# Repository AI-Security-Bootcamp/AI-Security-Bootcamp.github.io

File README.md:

# AI Security Bootcamp

Website for the AI Security Bootcamp, built with [Next.js](https://nextjs.org).

**Live site:** https://ai-security-bootcamp.github.io/

## Development

Use Node.js 24 (also used in CI) and npm. `package-lock.json` is the sole lockfile;
the obsolete pnpm lockfile has been removed.

```bash
npm ci
npm run dev
```

Open [http://localhost:3333](http://localhost:3333) to view the site.

Check dependency advisories with `npm audit`, including development tools. After
updates, run typechecking, lint, unit tests, and the production browser suite.
Next.js route parameters are asynchronous, and Tailwind 4's theme configuration
lives in `src/app/globals.css`.

The `serve` dependency currently pins `compression` to vulnerable version 1.8.1.
The scoped npm override selects patched 1.8.2 or later; remove it once `serve`
updates its dependency. See the [compression advisory](https://github.com/advisories/GHSA-vc2v-76pw-4v95).

Next's ESLint plugin uses `fast-glob` only for `globSync` root-directory discovery.
Its scoped override uses a small adapter in `tools/next-eslint-glob` backed by
Node's built-in `fs.globSync` (stable in Node 22.17+) to remove the unpatched
[`braces` vulnerability](https://github.com/advisories/GHSA-vfj7-8cjw-p6xm).
A unit test exercises that plugin integration; review the override when upgrading
`eslint-config-next` and remove it once upstream replaces the vulnerable chain.
ESLint stays on 9.39.5 because the React, import, and accessibility plugins still
declare ESLint 9 as their highest compatible major version.

## Deployment

The site automatically deploys to GitHub Pages when changes are pushed to the `main` branch via GitHub Actions.

To build locally:

```bash
npm run build
```

Static files are output to the `out/` directory.

## City program shortcuts

`/london`, `/sf` (or `/san-francisco`), `/vegas`, and
`/singapore` show that city's latest program and update the URL to its dated
program page, preserving query parameters and anchors. The latest program is
the one with the greatest start date across all years, including past, current,
and upcoming cohorts, regardless of whether applications are open.

City routes are generated from `src/lib/cohorts.ts` during each build. Register
each program component in `src/app/_program-pages.ts`; new location slugs get
their own city shortcut automatically. Alternate city names are defined in
`src/lib/city-programs.ts`. Year-specific aliases such as `/london26` and `/sf26`
continue to point to their original cohorts.

## Homepage film

The homepage uses `src/components/HeroFilm.tsx` and the versioned, static media
package in `public/video/aisb-hero-v5/`. No streaming service or server runtime is
needed: these files are included in the normal GitHub Pages export.

- The workshop thumbnail stays still and is clickable. The opening preloads
  through the bounded adaptive buffer, but playback requires a click or Enter.
- Playback starts with sound and the browser's standard controls; no duplicate
  toolbar, silent looping preview or automatic restart on scroll/tab return.
- The film pauses when offscreen or in a hidden tab. Resume is always explicit.
- Native HLS where supported; otherwise dynamically loaded `hls.js`, with
  automatic 360p/540p/720p/1080p quality switching and aligned two-second segments.
- The JavaScript player starts at 360p and caps quality to the displayed size;
  Safari's native player manages its own quality selection. A 540p
  fast-start MP4 is the fallback for unsupported HLS or fatal streaming errors.
- The same opt-in behavior applies to reduced motion, Save-Data and 2G users.
- The thumbnail is keyboard accessible and transfers focus to the native player.
  Burned-in captions and the music attribution in the media package remain.
  No separate transcript/credits row is displayed beneath the hero.

The thumbnail uses the original workshop photograph: instructor, raised hand and
attendees, with “A week at AISB” and a centered red, square play overlay rendered as HTML/CSS.
There is no location label or duration badge. The photograph and encoded film are unchanged.
On phones, the original larger typography is restored, with side-by-side buttons
and reduced top padding. Text, video and carousel follow their natural content
height with 24 px around the video, without stretching to fill tall screens.
The theme toggle floats independently with a 44 px touch target; desktop keeps the
spacious two-column hero.
The player preserves the full 16:9 picture rather than cropping the speakers or
captions. All 29 caption boxes have equal 16 px vertical padding in the master.

To encode a replacement from a corrected master and its lossless audio mix:

```bash
python3 videos/encode_web.py path/to/master.mp4 \
  --audio-master path/to/delivery-master.wav \
  --timeline path/to/timeline.json \
  --output public/video/aisb-hero-v6
```

Requires FFmpeg/ffprobe and Python 3.11+. The encoder refuses to overwrite an
existing package and verifies full decoding, aligned keyframes, source hashes,
and the MP4 fast-start header. Update `mediaRoot` in `HeroFilm.tsx` to the new
version after encoding. The current package's `encoding.json` records sizes and
checks. Retain the transcript and music credit when moving the files; an external
media host would also need appropriate CORS and HLS/MP4 content types.

The TypeScript browser suite covers preloading, responsive/dark-mode thumbnails,
keyboard activation, sound-on playback, seeking, no looping, explicit resume,
reduced motion/data saving, declined playback, HLS failure fallback, and a real
throttled bandwidth downshift. Native Safari playback still needs a real-device
check. Local tests and builds do not publish the site.

## Testing

Use Node.js 20.19+ (or 22.12+ / 24+) and npm. Install the test browser once:

```bash
npm ci
npx playwright install --with-deps --only-shell chromium
```

```bash
npm test                 # Vitest unit and server-rendered component tests
npm run test:watch       # Watch unit tests while editing
npm run typecheck        # Check application code, tests, and test configs
npm run test:e2e         # Build, start a static preview, run Chromium, then stop it
npm run test:e2e:ui      # Playwright's interactive test runner
npm run test:hero        # Only the homepage layout and video browser tests
npm run test:all         # Typecheck, unit tests, and all browser tests
```

Tests live in `tests/unit/*.test.ts` and `tests/e2e/*.spec.ts`. Vitest handles
TypeScript and JSX directly. Playwright provides isolated browser contexts,
shared fixtures, named tests, failure screenshots/traces, and an HTML report.
Browser tests serve the production export to exercise the same directory routes
as GitHub Pages. They block external requests, including analytics and live forms.
The slower bandwidth-adaptation check is included in the normal browser suite.

To target specific tests or use an existing server:

```bash
npm test -- city-programs
npm run test:e2e -- city-aliases
PLAYWRIGHT_BASE_URL=http://127.0.0.1:3333 npm run test:e2e
npx playwright show-report
```

Set `PLAYWRIGHT_CHROMIUM_EXECUTABLE` only if using an existing Chromium binary.
Artifacts go to ignored `test-results/` and `playwright-report/` directories.
Pull requests run typechecking, lint, unit tests, and browser tests. Main-branch
builds pass the same checks before deployment.

## Signup experiments (October 2026)

The homepage always lists cohorts accepting applications first and marks each
cohort's application status. The programme menu is labelled “View programmes”.

The **SF mobile Apply** experiment is running in PostHog project 324798:

| Experiment | Feature flag | Primary conversion |
| --- | --- | --- |
| [SF mobile Apply](https://us.posthog.com/project/324798/experiments/501073) | `signup-sf-mobile-apply-v1` | Click any Airtable application link; individual new CTA usage is secondary |

The flag uses equal `control` / `test` variants. The treatment adds a fixed bottom
Apply button and another after Cost & Selection. Mobile eligibility is determined
at page load with a viewport below 768 CSS pixels. The buttons hide on wider
screens after resizing.

The [homepage essentials](https://us.posthog.com/project/324798/experiments/501071)
and [SF essentials](https://us.posthog.com/project/324798/experiments/501072) tests
were stopped on 21 October 2026, and their flags were disabled. The summary blocks
and their assignment code have been removed. Their historical results remain in
PostHog; the early samples were insufficient for a reliable conversion conclusion.

`src/lib/mobile-apply-experiment.ts` reads the mobile flag without the SDK's
automatic exposure event. It emits `signup_experiment_exposed` after the assigned
UI is committed, with `experiment`, `variant`, `page`, `mobile_apply_variant`, and
`$feature/<flag-key>` properties. Missing, disabled or blocked flags retain the
normal page and emit no exposure. The
PostHog experiment uses that custom exposure, production host filters, exclusion
of test accounts and a 30-minute conversion window. The application CTAs also emit
`application_form_clicked` for actual form destinations, while keeping existing
click events and adding `cohort_id`, `destination` and `href` to them.

Analytics keeps `persistence: 'memory'`. Assignment stays fixed for the current
page load; a reload or document navigation can produce a new identity/variant.
These are **page-load comparisons, not unique-person or completed-application
conversion rates**. Do not join homepage and SF loads as a cross-page funnel.
Before 21 October at 22:44 UTC, the mobile test could overlap with the SF essentials
test. Keep that change in context when comparing results before and after removal.
The small mobile audience may not yield a conclusive result before applications
close. Secondary CTA usage alone is not evidence of overall improvement.

Check exposure balance and production application-link events before interpreting
results. End the mobile test by **8 November 2026 at 11:59:59 UTC** (the 7 November AoE
deadline). The client also stops enrolling new page loads after that deadline or
when the SF cohort's application mode is closed. Disable the corresponding flag
to return new loads to the original layout. Do not persist analytics IDs to make
assignments sticky without a separate privacy decision.

`tests/e2e/signup-experiments.spec.ts` mocks PostHog and intercepts all analytics
traffic. It checks control/treatment exposures, delayed and disabled flags,
mobile and desktop eligibility, the deadline, CTA destinations, footer clearance
and the existing cookie/localStorage behaviour.

## Video-generation source

The reusable renderers, edit plans, selections and review templates are in
[videos/](videos/README.md), with one flat folder per edit and shared helpers.
Run `python3 videos/run.py list` to see the available commands. Raw/private inputs
and generated assets stay in the ignored media workspace; they are not needed in
Git. The previous `scripts/encode-hero.py` command remains a compatibility wrapper.

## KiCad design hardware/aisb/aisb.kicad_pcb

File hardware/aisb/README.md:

# AISB e-paper badge

The current saved design is `aisb.kicad_pcb`, with project settings in
`aisb.kicad_pro`. Earlier Vegas/London copies are preserved in Git; see
[hardware history and layout](../README.md). Commit revisions to these stable
filenames. The design notes below describe the original prototype architecture;
the saved PCB includes subsequent manual KiCad edits.

## Render badge images

With Python 3 and Pillow installed, run from the repository root:

```bash
python3 hardware/aisb/scripts/render-web-badge.py \
  --first-name Pranav --last-name Gade --role speaker
```

The bundled font and website logo are selected automatically. Black/red flashing
planes and a matching preview go to the ignored `out/flash/` directory. Use
`--output-dir` to choose another location. Monochrome nametags use
`scripts/render-nametag.py`; arbitrary artwork uses `scripts/render-three-color-art.py`.
The source for the balloon artwork is `assets/artwork/girl-with-balloon.jpg`.

The three-color panel writer is `scripts/write_image_b.py`; it expects the
Waveshare driver checkout under `scripts/driver/` on the programming machine.
The monochrome programmer and its setup instructions are in `firmware/`.

### Small 250 × 122 name-only badge

```bash
python3 hardware/aisb/scripts/render-small-badge.py --name "Byron Alvarez"
```

This separate layout uses IBM Plex Mono Bold, all caps, black text on white,
and nothing else. It fits one or two lines using actual ink bounds, centers
them with 10px minimum margins, and saves a true 1-bit PNG to `out/small/`.
It never accesses the Pi or a display. The existing 360 × 240 flash helper
is **not compatible**. A separate `write_image_2in13_v4.py` and the recovery
kit's `flash-small-badge.sh` support the confirmed Waveshare 2.13-inch V4
monochrome panel; see [setup and switch settings](../epaper/README.md).
Tests: `python3 hardware/aisb/scripts/test-small-badge.py`.

## Hardware overview

This revision is a 100 x 145 mm conference badge built around the
[Waveshare 3.52-inch raw black/white e-paper panel](https://www.waveshare.com/3.52inch-e-paper.htm).
The screen is large enough for a readable name and role, while the upper PCB
remains visible for the AISB logo and copper artwork.

The badge has no microcontroller, USB connector, battery, MIDI keys, or touch
controls fitted by default. Instead:

- the 360 x 240 e-paper glass is centred on the front of the badge;
- its actual 3.65 +/- 0.30 mm electrical FPC, as dimensioned in the
  [Waveshare V1.1 panel drawing](https://files.waveshare.com/wiki/3.52inch%20e-Paper%20HAT/3.52inch%20e-Paper%20V1.1.pdf), stays straight into a low-profile
  front-side ZIF immediately left of the glass; the drawing's 10 mm feature is
  only a removable adhesive-tape pull-tab, and there is no internal flex
  cutout;
- the badge carries the small passive high-voltage support circuit required by
  the raw panel;
- a reusable external programmer supplies 3.3 V, ground, and SPI/control through
  the zero-height Tag-Connect `J3` target;
- optional `J4` is a passive 1 x 8, 2.54 mm through-hole interface for a short
  ribbon harness to a removable Waveshare ESP32 Driver Board V3; the module is
  powered only through its own USB-C connector, its onboard FPC stays empty,
  and the carrier provides only passive slots and a nonconductive spacer/retainer;
- a standard-polarity rear-silkscreen QR links to `https://aisb.dev/badge0`; and
- a two-layer PCB pickup coil remains available as a passive electromagnetic
  audio sensor.

After an external programmer refreshes the screen and is removed, the image
remains visible without power. Each badge therefore needs the comparatively
expensive controller only while its name is being written.

## Important status

This is a prototype design, not a production release. The current 24-pin panel
table and an older application-circuit drawing in Waveshare's documentation
are not completely consistent. Before ordering production quantity:

1. Buy one exact panel SKU/revision and the proposed 24-position ZIF.
2. Verify the flex contact side, pin 1, insertion direction, glass dimensions,
   and complete straight-tail/connector fit against the physical parts.
3. Assemble 3-5 badges and validate every generated e-paper rail during a
   refresh with a current-limited bench supply.
4. Confirm that the display survives repeated mounting and programming cycles.
5. Run KiCad DRC and have an experienced PCB designer review the high-voltage
   support circuit, footprint geometry, and assembly files.
6. If the optional ESP32 path is considered, measure at least three exact Rev 3
   modules, continuity-test the passive harness, and validate the mounting
   slots/spacer, USB clearance, retention/drop loads, and worn-badge RF range.
   There is no onboard power isolation: never attach or power two controllers.

Do not send the generated board straight to a production run.

For the current two-week deadline, follow
[`docs/two-week-release-plan.md`](docs/two-week-release-plan.md). The custom
on-board circuit remains the primary path, with five engineering units tested
first. Every raw panel is also pre-written off-board before mounting. Two
official Waveshare Driver HAT stations provide an independent fallback by
writing the raw panel flex directly; they do not bypass the badge through
`J3`. See [`docs/hat-fallback.md`](docs/hat-fallback.md).

For the two-week schedule, buy **both types of universal driver**: two
[Universal Driver HATs](https://www.waveshare.com/e-paper-driver-hat.htm) as the
Raspberry-Pi-friendly production fallback, and at least three exact
[ESP32 Driver Board V3](https://www.waveshare.com/e-paper-esp32-driver-board.htm)
samples for dimensional spread, passive-harness validation, and
participant-add-on experiments. Waveshare's 3.52-inch panel page recommends
both, but the ESP32
product page's current support table does not explicitly list 3.52 inches, so
do not depend on the optional module until the exact parts pass the complete
physical, electrical, and repeated-refresh gates.

## Open the design in KiCad

1. Install KiCad 10 or newer. The rear QR uses KiCad's native barcode object.
2. In KiCad's main window choose **File > Open Existing Project**.
3. Select `aisb.kicad_pro` in this directory.
4. Double-click **PCB Editor** to inspect the board. The circuit reference is
   the legacy `aisb.sch`; open that file from Schematic Editor and
   let KiCad convert it when prompted.
5. In PCB Editor, press **B** once to refill the rear ground zone, then run
   **Inspect > Design Rules Checker**.
6. Press **Alt+3** (or choose **View > 3D Viewer**) for the
   board preview.

Do not run **Update PCB from Schematic**. The saved board includes manual edits
after the original `scripts/generate-board.mjs` output; the legacy schematic is
an electrical reference rather than its netlist source.

The PCB outline, footprints, copper, pads, and silkscreen are in the KiCad
source. Vendor 3D models are not assigned to every custom footprint, so
KiCad may omit the glass, ZIF, or reusable programming cable. The OpenSCAD model
shows the original intended assembled form.

## Layout

```text
front, 100 x 145 mm

      lanyard hole
  +------------------+
  | passive PCB coil |  <- copper artwork / EM pickup
  |      AISB.       |
  |------------------|
  |  3.52-inch raw   |  <- 360 x 240 persistent name/role
  |  e-paper glass   |
  |                  |
  +------------------+

front: centred panel plus short-flex ZIF beneath the left service spine
back:  passive e-paper support parts, audio pads, a connector-free
       Tag-Connect target, rear QR, optional DNP 1 x 8 J4, and passive module mounting
```

The panel is centred at `(50.00, 94.205)` mm, so its 84.70 mm landscape width
runs from `x=7.65` to `x=92.35` mm. Front-side `J1` sits immediately left of
the glass and uses the
[Hirose FH34SRJ-24S-0.5SH](https://www.hirose.com/en/product/p/CL0580-1255-6-50)
candidate, rotated 270 degrees so its mouth faces right. Its mouth is
near `x=5.50`, body spans about `x=1.70..5.50`, signal-pad row is near
`x=5.00`, and retention row is near `x=1.70`. The inserted tail tip reaches
`x=4.00`, giving 1.50 mm nominal insertion past the mouth. The short electrical
FPC crosses the small gap without bending. The PCB remains solid beneath the
glass and has no display or flex-tail cutout.

The custom `J1` footprint numbers its pads by the Waveshare panel contacts
(panel pin 1 at the top of the landscape tail). In this right-facing use that
sequence is mirrored relative to the Hirose terminal numbering. Follow the PCB
panel-pin marking, not the connector body's polarity mark, and continuity-check
the first physical assembly before applying power.

The intended no-hole mount looks like a small instrument viewport: a black
PETG spacer/bezel surrounds the glass, a 0.5 mm clear hard-coated polycarbonate
lens protects it, and thin perimeter transfer adhesive holds the stack. An
opaque removable all-plastic left service spine, keyed to the bezel, hides and
protects the front connector while preserving access to `J1`. Do not use
magnets or steel clips; they would disturb the passive magnetic pickup.

## Files

- `aisb.kicad_pcb` - current saved KiCad PCB source.
- `aisb.kicad_sch` - converted electrical-reference schematic.
- `aisb.sch` - legacy KiCad schematic, importable by current KiCad.
- `assets/aisb-wordmark.svg` - font-independent official AISB vector master.
- `scripts/generate-board.mjs` - deterministic PCB/preview generator.
- `scripts/badge-qr-geometry.mjs` - fixed, self-checking Version 2-M QR matrix.
- `scripts/validate-artwork.mjs` - validates the enlarged logo and rear QR.
- `out/flash/` - generated flashing planes and retained badge previews (ignored).
- `out/gerbers/` - fabrication exports (ignored).
- `docs/manufacturing.md` - factory/manual split, prototype gates, and costs.
- `docs/jlcpcb-prototype-order.md` - JLCPCB engineering-order settings, export
  procedure, and CAM/placement acceptance checklist.
- `docs/pinout.md` - programmer, raw-panel, audio, and update connections.
- `docs/pickup-design.md` - pickup geometry, calculations, use, and test plan.
- `cad/aisb.scad` - parametric visualization model.
- `cad/viewport-cut-template.svg` - 1:1 lens, spacer, and underside-print template.
- `bom.csv` - prototype bill of materials.
- `bom-tooling.csv` - reusable equipment for both programming paths.
- `firmware/` - shared XIAO ESP32-S3 registration-station programmer and PBM
  upload utility; the XIAO is tooling, not installed on each badge.

The original parametric generator and its checks remain available for reference.
Generate and validate that design with:

```bash
node hardware/aisb/scripts/generate-board.mjs
node hardware/aisb/scripts/validate-generated.mjs
node hardware/aisb/scripts/validate-artwork.mjs
```

The generator writes its board and placement preview to `out/generated/`.
The validators default to that generated board; an explicit PCB path can be
passed as their first argument. These checks cover the original generator
design, not the later manual revisions. `BADGE_OUTPUT_ROOT` overrides the
generator destination. Keep the current `aisb.kicad_pcb` under version control
and inspect it in KiCad when validating the saved design.

## Programming architecture

The rear `J3` pads mate with a reusable TC2050-IDC-NL spring-pin ribbon cable;
nothing is soldered there on each badge. The external programmer must provide
a regulated 3.3 V rail plus MOSI, SCLK, CS, D/C, reset, and the active-low BUSY
input. It must never apply 5 V.

The panel's raw 24-conductor tail is **not** the exposed SPI interface. It also
carries its internal gate/source drive and boosted display rails, so it stays
connected to low-profile front-side ZIF `J1` immediately left of the glass.
See `docs/pinout.md` for the exact separation.

### Optional removable rear ESP32 controller

> **NOT PRODUCTION RELEASED:** `J4`, its harness, and the passive module mount
> remain optional. Qualify the exact delivered module, pin map, USB clearance,
> retention/drop behavior, and worn-badge RF range before participant use.

The physical-rear-right bay accepts the current `29.46 x 48.25 mm` Waveshare
e-Paper ESP32 Driver Board V3 in passive carrier slots with a removable,
nonconductive spacer/retainer. It does not plug electrically into the carrier.
Keep its USB-C connector accessible below the badge edge and its antenna end
clear. The module's onboard 24-pin FPC connector stays empty: the one raw panel
remains connected only to front-side badge `J1`.

Optional badge `J4` is one row of eight 2.54 mm plated holes. Populate a simple
1 x 8 male header only on equipped badges, or solder a short harness directly
to the holes. A short 8-way female-female Dupont ribbon can mate to the badge
header and split into individual female sockets at the Waveshare end. Its badge
pin order is `1=3V3`, `2=GND`, `3=BUSY`, `4=RST`, `5=DC`, `6=CS`, `7=MOSI`,
`8=SCLK`; [`docs/pinout.md`](docs/pinout.md) gives the exact Waveshare `J3/J4`
header mapping. Label pin 1 and continuity-test every harness before use.

This is a deliberately passive interface: there is no onboard current limiter,
power mux, buffer, or controller arbitration. The Waveshare board is powered
only by its own USB-C connector, and its `VDD3V3` output supplies badge `3V3`
through `J4-1`. Remove the Tag-Connect probe and every other supply before
connecting the harness. Connect and disconnect only while fully unpowered, and
never attach or power two controllers at once.

Published Rev 3 hardware leaves GPIO4's `R35` link DNP, and this badge does not
connect GPIO4. Firmware therefore cannot switch off the USB-powered target; a
successful update means the panel entered deep sleep while the module and badge
rail remain powered. Disconnect USB-C before removing the harness. Set the
module's USB-to-UART switch 2 **ON** for its CH343 bridge. Test at least 20
refresh/sleep cycles, BUSY-timeout recovery, harness strain relief, USB cable
side-load, retention, shake/drop, and radio range on a fully stacked worn badge.

## Passive pickup

The upper copper artwork is a 30-turn-per-layer, series-aiding magnetic search
coil. Its large chamfered rectangle uses the badge's available area more
effectively than a circular loop. The theoretical open-circuit pickup is about
1.9x the original 12-turn-per-layer revision. Ground pours are explicitly kept
out of the winding area. Production turns remain under continuous black solder
mask so fingers, sweat, or metal badges cannot bridge adjacent turns; renders
show their path more strongly only so the shape is understandable.

Hold the upper half near a laptop, display cable, charger, motor, or other
low-voltage electronic device, then rotate the badge for the loudest result.
Record through a microphone input or USB microphone adapter. `C1` is 4.7uF to
preserve 50/60Hz content while blocking microphone bias, `R1` provides the
nominal headset-microphone detection load, and `R2` joins the two spiral layers.
Use a short twisted or shielded audio pigtail, and do not refresh the e-paper
while recording.

See `docs/pickup-design.md` for the shape comparison, predicted sensitivity,
CTIA wiring, and prototype acceptance tests.

It is a sensor, not test equipment. Never touch it to exposed conductors or use
it inside mains-powered equipment.

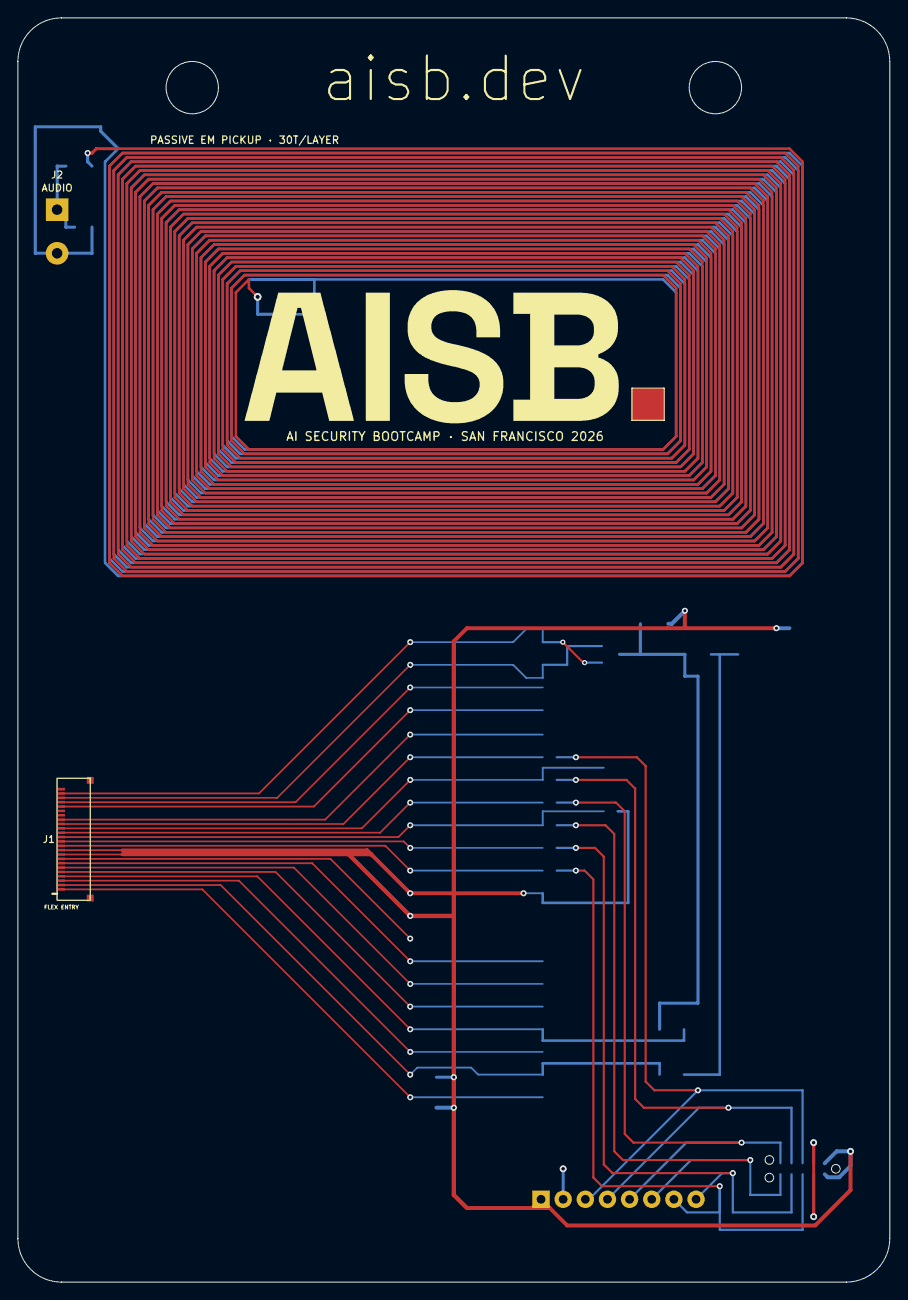
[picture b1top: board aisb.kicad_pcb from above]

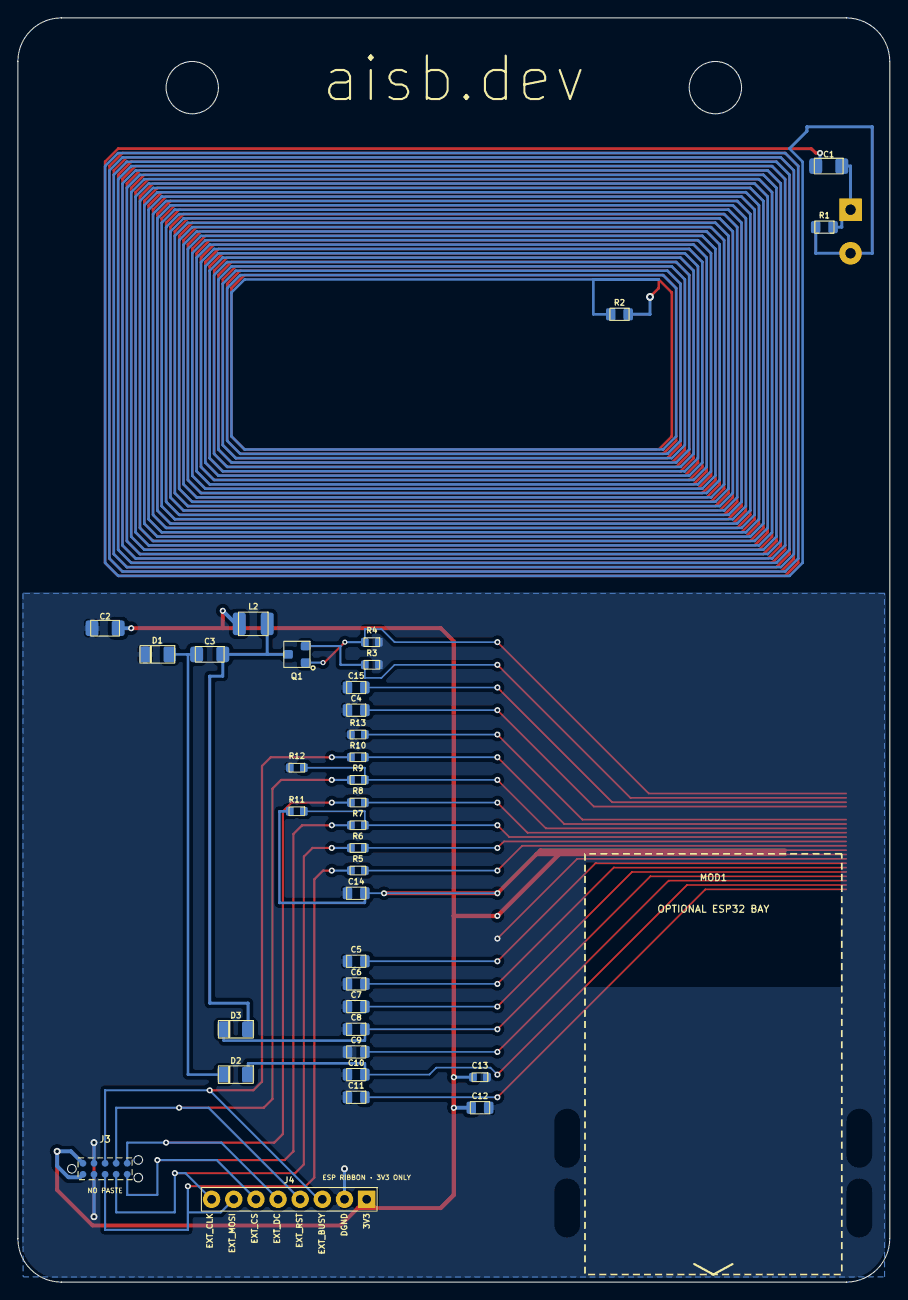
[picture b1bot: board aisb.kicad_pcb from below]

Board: 2 copper layers, 100.0 x 145.0 mm, 41 parts (37 on the bottom side), 31 nets.

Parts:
C1: 4.7uF; 1206_C1
C2: 4.7uF 50V; 1206_C2
C3: 4.7uF 50V; 1206_C3
C4: 1uF 25V; 0805_C4
C5: 1uF 10V; 0805_C5
C6: 1uF 25V; 0805_C6
C7: 1uF 25V; 0805_C7
C8: 1uF 25V; 0805_C8
C9: 1uF 25V; 0805_C9
C10: 1uF 25V; 0805_C10
C11: 1uF 25V; 0805_C11
C12: 10uF 10V; 0805_C12
C13: 100nF; 0603_C13
C14: 1uF 10V; 0805_C14
C15: 1uF 25V / DNP; 0805_C15
D1, D2, D3: MBR0530; D_SOD-123
EPD1: WAVESHARE 3.52in RAW E-PAPER / 240x360; Waveshare_3.52in_Raw_Panel
J1: FH34SRJ-24S-0.5SH(50)/(99) / DISPLAY-NUMBERED / V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; Hirose_FH34SRJ-24S-0.5SH_24P_P0.50mm_Horizontal
J2: AUDIO; Audio_Pigtail_2Pin
J3: TC2050-IDC-NL / DNL; Tag-Connect_TC2050-IDC-NL_2x05_P1.27mm_Vertical
J4: 1x08 P2.54 / OPTIONAL / DNP; ESP_Ribbon_1x08_P2.54mm
L1: 30T_X2_CHAMFERED_SEARCH_COIL; Generated_PCB_Spiral
L2: 68uH; 1210_L2
MH1: 4x 2.2x6 NPTH CRADLE SLOTS; ESP32_Cradle_Strap_Slots
MOD1: WAVESHARE E-PAPER ESP32 DRIVER BOARD V3 / OPTIONAL; Waveshare_ESP32_Driver_Board_V3_Header_Clear_Cradle_Bay
Q1: BSS138; SOT-23
R1: 4.99k; 0805_R1
R2: 0R; 0805_R2
R3: 3R; 0603_R3
R4: 10k; 0603_R4
R5: 100R; 0603_R5
R6: 100R; 0603_R6
R7: 100R; 0603_R7
R8: 100R; 0603_R8
R9: 100R; 0603_R9
R10: 1k; 0603_R10
R11: 100k; 0603_R11
R12: 100k; 0603_R12
R13: 0R; 0603_R13

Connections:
3V3: C2.1, C12.2, C13.2, C14.1, J1.15, J1.16, J3.1, J3.10, J4.1, L2.2, R11.2
AUDIO_GND: J2.2, R1.2, R2.2
AUDIO_SIG: C1.1, J2.1, R1.1
BS: J1.8, R13.1
CFLY: C3.2, D1.2, D2.1
DGND: C2.2, C4.2, C5.2, C6.2, C7.2, C8.2, C9.2, C10.2, C11.2, C12.1, C13.1, C14.2, C15.2, D1.1, J1.17, J3.2, J3.9, J4.2, R3.1, R4.1, R12.2, R13.2
EPD_BUSY: J1.9, R10.1
EPD_CLK: J1.13, R6.1
EPD_CS: J1.12, R7.1, R11.1
EPD_DC: J1.11, R8.1
EPD_MOSI: J1.14, R5.1
EPD_RST: J1.10, R9.1, R12.1
EXT_BUSY: J3.8, J4.3, R10.2
EXT_CLK: J3.4, J4.8, R6.2
EXT_CS: J3.5, J4.6, R7.2
EXT_DC: J3.6, J4.5, R8.2
EXT_MOSI: J3.3, J4.7, R5.2
EXT_RST: J3.7, J4.4, R9.2
GDR: J1.2, Q1.1, R4.2
LEGACY_NC: C15.1, J1.4
PICKUP_A: C1.2, R2.1
RESE: J1.3, Q1.2, R3.2
SW: C3.1, D3.2, L2.1, Q1.3
VCOM: C11.1, J1.24
VDDD: C5.1, J1.18
VDHR: C4.1, J1.5
VGH: C8.1, D3.1, J1.21
VGL: C10.1, D2.2, J1.23
VPP: C6.1, J1.19
VSH: C7.1, J1.20
VSL: C9.1, J1.22

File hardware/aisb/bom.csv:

Reference,Quantity,Description,Suggested part/package,Populate,Notes
EPD1,1,3.52-inch 360x240 black/white raw e-paper panel,Waveshare SKU 22609 / 3.52inch e-Paper,Manual,"Raw glass with 24-contact 0.5mm FPC protruding 3.65+/-0.30mm; drawing's separate 10mm feature is a removable adhesive-tape pull-tab; confirm exact revision"
J1,1,24-position 0.5mm-pitch dual-contact low-profile FPC ZIF,"Candidate Hirose FH34SRJ-24S-0.5SH(50) or (99)",Yes,"Front side immediately left of glass; rotate 270deg/right-facing: mouth x~5.50 body x~1.70..5.50 signal-pad row x~5.00 retention row x~1.70; inserted tail tip x~4.00 gives 1.50mm nominal insertion; custom pads are numbered by Waveshare panel contact and mirror the Hirose terminal sequence; 1.0mm high for 0.3mm FPC; physically dry-fit and continuity-map contact side pin 1 and straight-tail reach; panel drawing's 2mm LUS67-35024-3100 is unavailable"
J3,1,10-pad no-legs programming target,Tag-Connect TC2050-IDC-NL footprint,PCB feature,"Do not populate; cable and XIAO programmer are reusable tooling; pins 1/10 are the same badge 3V3 rail; attach only while every other controller and power source is disconnected"
J4,1,8-position 2.54mm through-hole SPI header footprint,"1x8 breakaway male header, 2.54mm pitch",No,"Optional/DNP participant interface; bare plated holes also accept direct-soldered wires; pin order 1=3V3 2=GND 3=BUSY 4=RST 5=DC 6=CS 7=MOSI 8=SCLK; no onboard protection or controller arbitration"
MOD1,1 per optional controller,Removable e-paper ESP32 Driver Board V3,Waveshare SKU 15823,Manual,"Not soldered or socketed to the badge; power only through module USB-C; connect through the passive J4 harness; onboard 24-pin FPC stays empty; only one controller may be attached/powered; official source https://www.waveshare.com/e-paper-esp32-driver-board.htm"
Q1,1,N-channel MOSFET,BSS138 SOT-23,Yes,E-paper boost switch
L2,1,68uH shielded inductor,"1210/3225; >=150mA saturation",Yes,E-paper boost inductor
D1-D3,3,30V Schottky diode,MBR0530 SOD-123,Yes,E-paper charge pump
R3,1,3R resistor,0603 1%,Yes,RESE current sense
R4,1,10k resistor,0603 1%,Yes,GDR pull-down
R5-R9,5,100R resistor,0603 1%,Yes,"Series damping for MOSI SCLK CS_N DC and RST_N"
R10,1,1k resistor,0603 1%,Yes,BUSY_N series protection
R11,1,100k resistor,0603 1%,Yes,CS_N pull-up
R12,1,100k resistor,0603 1%,Yes,"RST_N pull-down keeps panel reset while programmer is absent"
R13,1,0R resistor,0603,Yes,BS strap selects 4-wire SPI
C2-C3,2,4.7uF 50V X7R capacitor,1206,Yes,"3V3 input reservoir and boost flying capacitor"
C4,1,1uF 25V X5R/X7R capacitor,0805,Yes,VDHR reservoir
C5,1,1uF 10V X5R/X7R capacitor,0805,Yes,VDDD reservoir
C6-C11,6,1uF 25V X5R/X7R capacitor,0805,Yes,"VPP VSH VGH VSL VGL and VCOM reservoirs"
C12,1,10uF 10V X5R/X7R capacitor,0805,Yes,Badge 3V3 interface bulk capacitor
C13,1,100nF 10V X7R capacitor,0603,Yes,Badge 3V3 interface bypass capacitor
C14,1,1uF 10V X5R/X7R capacitor,0805,Yes,Panel VDD/VDDIO decoupling
C15,1,1uF 25V capacitor,0805,No,"DNP legacy pin-4 option; current V1.1 pin table marks pin 4 NC"
L1,1,Two-layer 30-turn-per-layer chamfered rectangular pickup coil,"PCB feature; 0.30mm trace / 0.20mm space",No,"Fabricated copper with a padless PCB reference marker; no assembly part; no pour/thieving in x=8..92mm y=13..65mm"
C1,1,4.7uF 10V X7R capacitor,1206,Yes,"DC blocks headset microphone bias; larger value preserves 50/60Hz response"
R1,1,4.99k 1% resistor,0805,Yes,"Nominal CTIA microphone-detection load; DNP only for a verified high-impedance line/instrument-input build"
R2,1,0R resistor,0805,Yes,"Joins inner ends of top and bottom pickup spirals; retain for winding continuity test"
J2,1,2-pin audio pigtail connection,5.0mm-centre wire pads,Manual,"Audio signal and isolated audio ground; use a short twisted or shielded pigtail"
PROTECTOR,1,"Approx. 88x58mm 0.5mm clear hard-coated polycarbonate lens",Custom cut,Manual,"Protects front-mounted e-paper glass; no mounting holes"
BEZEL,1,Black PETG instrument-viewport spacer/bezel,Custom cut,Manual,"Perimeter support only; keep pressure and adhesive out of active area; no magnets or steel"
SERVICE-SPINE,1,Opaque removable black left service spine,3D-printed PETG part,Manual,"All-plastic spine keyed to bezel; covers front-side J1 and straight FPC while preserving latch access; must not pinch flex; no magnets or steel"
ADHESIVE,1,0.05-0.10mm transfer adhesive perimeter frame,3M 467MP/468MP or qualified equivalent,Manual,"Keep adhesive out of active area straight-FPC path J1 latch and service-spine joint"
KAPTON,1,Removable polyimide tape,Generic,Manual,"Prototype retention or insulation only; do not cover J1 latch or bend the FPC"
LANYARD,1,Single-hook lanyard or cord loop,Generic,Manual,Board includes one centred 6mm circular lanyard hole
ESP-HARNESS,1 per optional controller,8-way female-female 2.54mm Dupont ribbon,"Short 1x8 female ribbon, split into individual female sockets at module end",Manual,"Badge end mates with optional J4 male header; module end maps J4-1..8 to Waveshare J3-1 J3-14 J3-9 J3-10 J3-11 J4-16 J3-12 J3-15; keep short and label both connector families and pin 1"
ESP-MOUNT,1 per optional controller,Nonconductive removable spacer/retainer,Custom PETG/nylon part,Manual,"Uses only the reviewed passive mounting slots; supports the removable Waveshare V3 board with USB-C accessible and antenna clear; no electrical sockets magnets or steel"
TOOL-CABLE,2 per build,10-pin no-legs spring-pin ribbon cable,Tag-Connect TC2050-IDC-NL,Tooling,"One per XIAO station; reusable; official source https://www.tag-connect.com/product/tc2050-idc-nl-10-pin-no-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"
TOOL-MCU,2 per build,Reusable custom-programmer MCU,Seeed XIAO ESP32-S3,Tooling,"Primary registration-station controller; any ESP32/RP2040/STM32 or other controller requires separate firmware wiring power-sequence and first-article qualification; official source https://www.seeedstudio.com/XIAO-ESP32S3-p-5627.html"
TOOL-HAT,2 per build,Universal e-Paper Raw Panel Driver HAT,Waveshare SKU 13512 / e-Paper Driver HAT,Tooling,"Two independent backup stations; each connects to raw panel flex through its adapter not badge J3; official source https://www.waveshare.com/e-paper-driver-hat.htm"
TOOL-ESP32,3 per build,Universal e-Paper Raw Panel Driver Board with WiFi/Bluetooth,Waveshare SKU 15823 / e-Paper ESP32 Driver Board V3,Tooling,"Three exact V3 validation/removable-controller units; power only through each board's USB-C and connect to badge J4 through the passive 8-wire harness; onboard 24-pin FPC remains empty; official source https://www.waveshare.com/e-paper-esp32-driver-board.htm"
TOOL-ESP-HARNESS,3 per build,Passive 8-wire ESP32-to-badge harness,"Female-female 2.54mm Dupont ribbon plus labels",Tooling,"One working assembly one mechanically stressed test assembly and one spare; split the module end to the exact Waveshare J3/J4 pins; continuity-test every conductor before use"
TOOL-REF-HAT,1-2 per build,Complete 3.52-inch e-Paper HAT,Waveshare SKU 22698 / 3.52inch e-Paper HAT,Tooling,"Known-working reference or emergency complete display; not a thin drop-in badge module; official source https://www.waveshare.com/3.52inch-e-paper-hat.htm"

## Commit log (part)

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2025-12-04 init commit
2025-12-10 update for after the program
2025-12-30 diana's project
2025-12-30 fix the description
2026-02-10 sg-2026
2026-02-12 singapore
2026-02-12 more variations
2026-02-12 some small rewording
2026-02-13 anohter version
2026-02-13 add application link
2026-02-13 more updates
2026-02-14 sash logo
2026-02-14 sash website
2026-02-23 countdown
2026-02-25 final updates
2026-02-26 posthog
2026-02-26 gtag and more posthog
2026-03-05 logos
2026-03-05 some text updates
2026-03-06 small text update
2026-05-13 redo some styling
2026-06-02 small updates
2026-06-05 add the canonical logos
2026-06-26 london updates
